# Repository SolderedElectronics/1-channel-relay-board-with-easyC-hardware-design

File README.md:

# 1-channel relay board qwiic Hardware Design

## About the Product

|  |
| :----------------------------------------------------------: |
| [Buy 1-channel relay board qwiic](https://www.solde.red/333021) |

Did you ever wanted to turn on and off a device that needs large current or voltage? Whether operating on DC or AC, a relay is what you need. A relay is actually an electronic switch that is activated by a signal we send from a Dasduino or Arduino. This module further simplifies the whole process because it contains everything you need for the relay to work, and you just have to connect it to the microcontroller and power supply. You don’t have to think about voltages and currents, insulation between high and low voltage or grounding, everything is already taken care of on the board.

This board has easyC connector. Thanks to qwiic ecosystem, this board can be connected using off-the-shelf cables, without soldering. Controlling the is as simple as it gets, too.

---

## Repository Contents

This repository contains all design files for 1-channel relay board qwiic, organized as follows:

- **`CAD` folder**: Contains KiCAD design files, including:
  - Schematics
  - PCB layout
  - Panel PCB layout
  - Source 3D files in Fusion360, if any
  - All files are sorted by version with a detailed change log.
- **`OUTPUTS` folder**: Includes all production-ready files, such as:
  - Bill of Materials (BOM) and interactive BOM (iBOM)
  - PDF versions of schematics
  - 3D `.step` file of the board
  - 3D-printable models
  - Gerber files for PCB manufacturing
  - Image of the pinout of the board
  - Product image
  - Compliance, legal and generic sales documents

Refer to the `Change Log` in the CAD folder for details about updates between versions.

---

## Learn More About the Product

Beyond the repository, explore the following resources:

### Soldered Verify

The **Soldered Verify** system ensures every board you purchase from Soldered is fully functional. It also provides access to exclusive test data for your product. To get started, find the unique Soldered Verify ID on your product's packaging and enter the ID on the [Soldered Verify page](https://soldered.com/verify/) to access test results and additional product details.

### Soldered Community

Soldered Community is your go-to place for technical support. Our engineers track and answer all questions posted there, and it’s a great space for the maker community. Get answers to your questions and solutions for your challenges at [Soldered Community](https://soldered.com/community).

### solde.red

solde.red is an ultimate URL shortener and information hub. Access it by typing solde.red/ followed by your product SKU, e.g., [solde.red/333000](https://solde.red/333000), to find getting-started guides, datasheets, open-source hardware and software files, certifications, images, pinouts, and more. Read more about the shortener [here](https://solde.red/info/).

---

## Contributing

Contributions are welcome! Here’s how you can get involved:

- Submit pull requests to enhance the design or fix issues.
- Report bugs or problems by opening an issue.

We encourage community collaboration to make this product even better.

---

## About Soldered

[Soldered for Makers](https://soldered.com) specializes in designing and manufacturing electronic products tailored for enthusiasts, ranging from hobbyists to professionals. Our portfolio includes electronic boards, sensors, and actuators that are widely utilized in fields such as microelectronics, mechatronics, robotics, programming, and IoT. Every product we offer is designed in-house and built upon open-source hardware and software platforms. Proudly certified and manufactured within the European Union, our catalog likely includes the product you need for your project.

We complement these products with comprehensive tutorials and manuals, product descriptions, schematics, programming codes, and project examples. Our round-the-clock [customer and technical support](https://soldered.com/community) is available for all our products, irrespective of the sales channel. Soldered’s success and services reflect our maker community’s unwavering [trust](https://www.trustpilot.com/review/soldered.com), for which we are deeply grateful. Join our community and create using Soldered products.

---

## License

All Soldered open-source hardware (OSH) is under The TAPR Open Hardware License. Read more in the LICENSE file located in this repository.

**Disclaimer:**

No warranty - all designs in this repository are distributed in the hope that they will be useful, but without any warranty. They are provided "AS IS", therefore without warranty of any kind, either expressed or implied. The entire quality and performance of what you do with the contents of this repository are your responsibility. In no event Soldered Electronics will be liable for your damages, or losses, including any general, special, incidental, or consequential damage arising out of the use or inability to use the contents of this repository. 

---

## Have fun!

Thank you for your support from your fellow makers at Soldered Electronics.

Happy Making!

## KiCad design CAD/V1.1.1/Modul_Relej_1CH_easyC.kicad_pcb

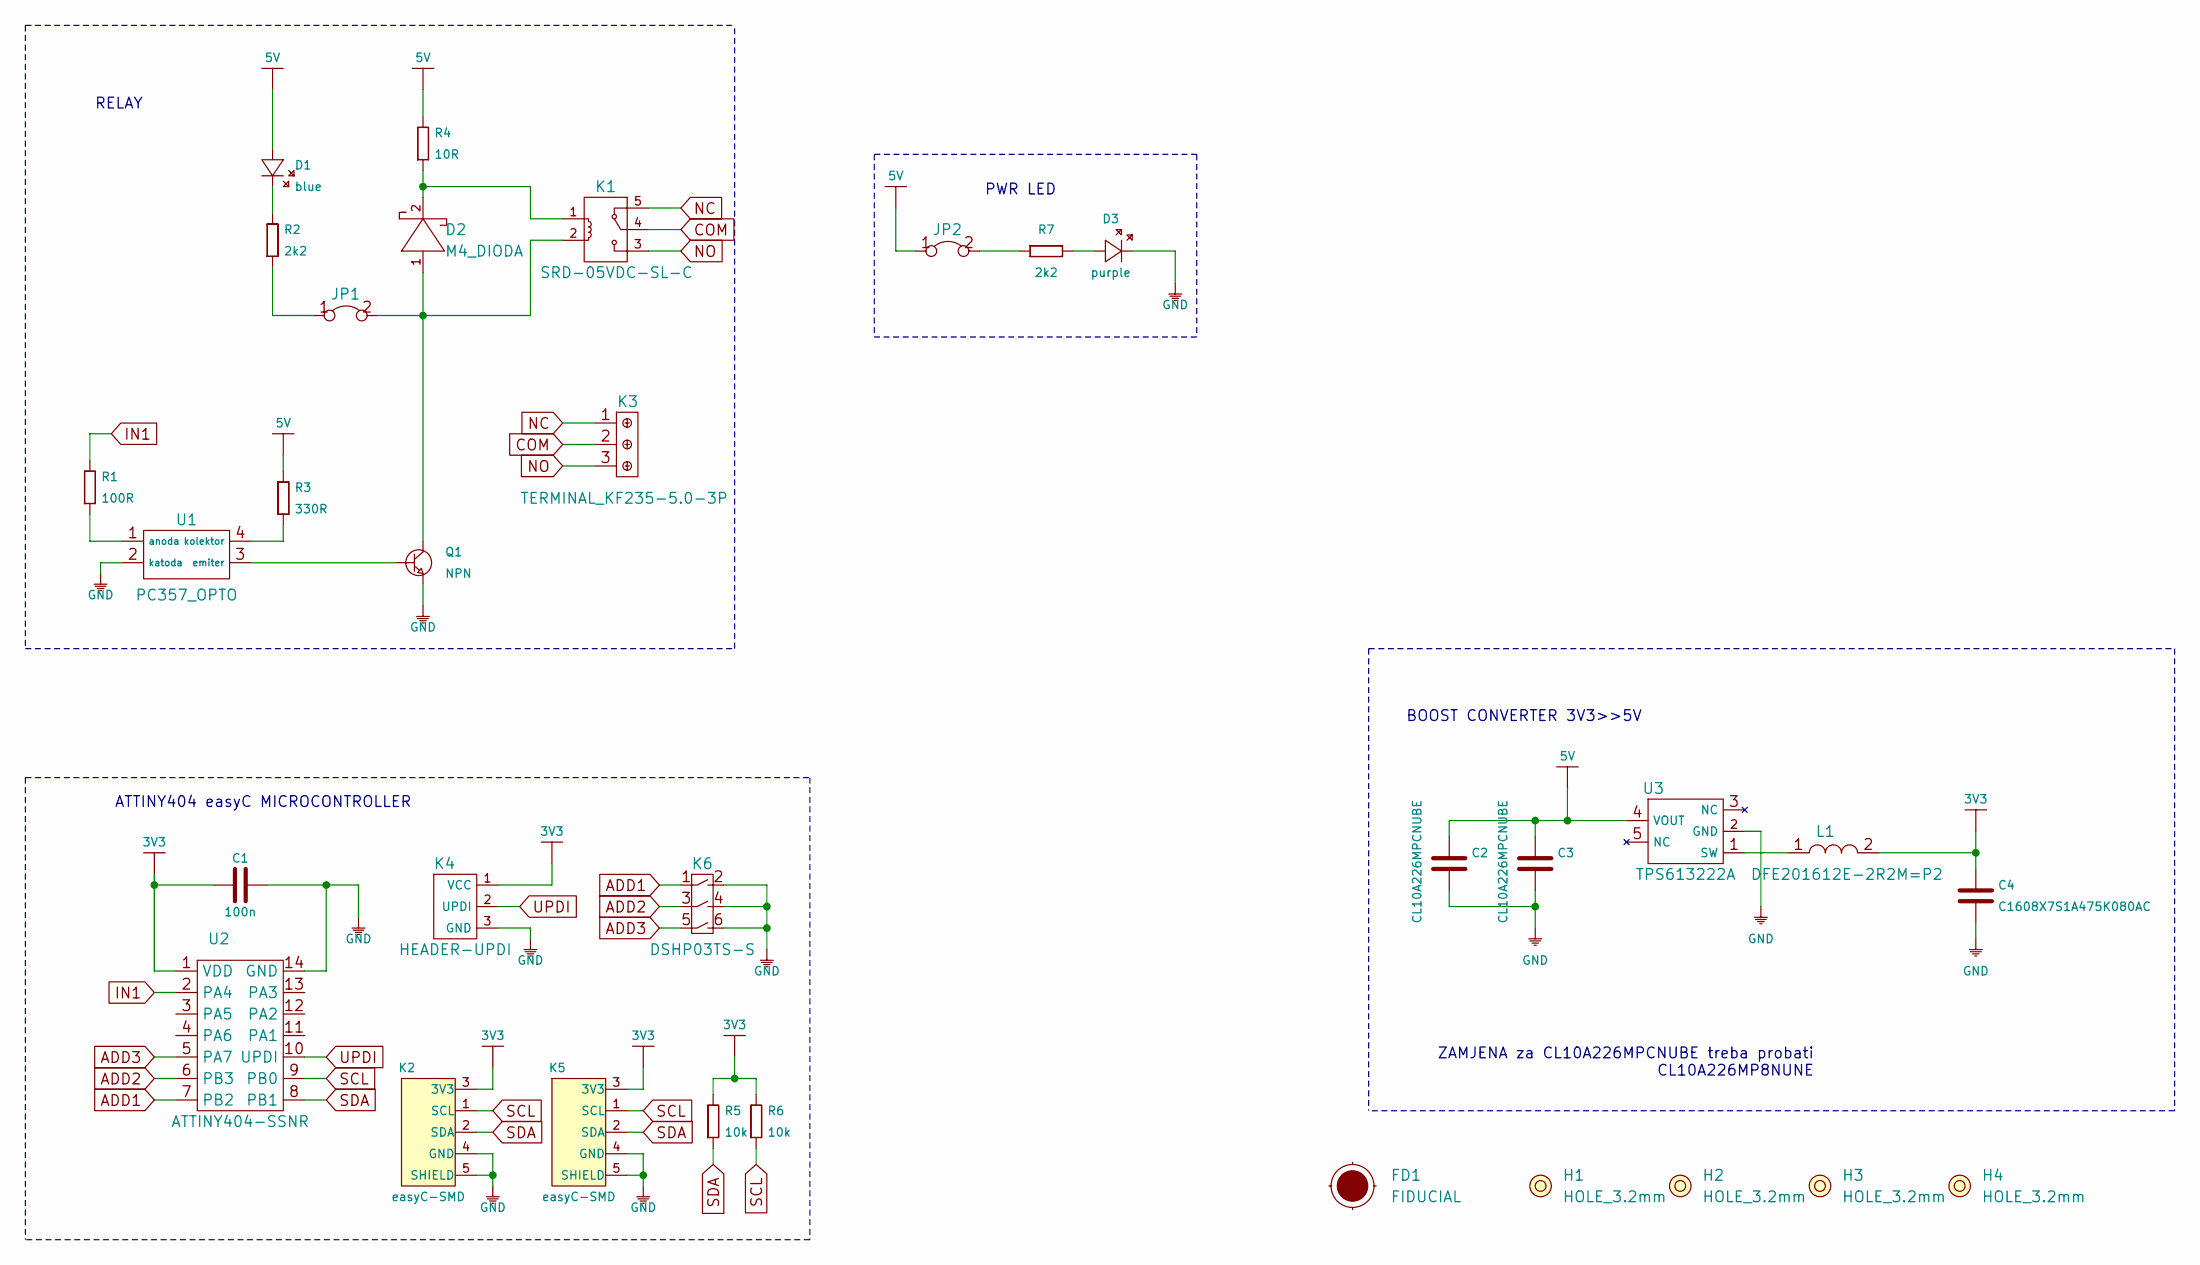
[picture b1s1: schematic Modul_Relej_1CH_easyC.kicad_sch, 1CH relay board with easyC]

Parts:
C1: 100n; 0603C
C2, C3: CL10A226MPCNUBE; 0603C
C4: C1608X7S1A475K080AC; 0603C
D1: blue; 0402LED
D2: M4_DIODA
D3: purple; 0402LED
FD1: FIDUCIAL; FIDUCIAL_23
H1, H2, H3, H4: HOLE_3.2mm
JP1, JP2: SMD-JUMPER-CONNECTED_TRACE_SLODERMASK
K1: SRD-05VDC-SL-C; SRD_RELAY_5V
K2, K5: easyC-SMD; easyC-connector
K3: TERMINAL_KF235-5.0-3P
K4: HEADER-UPDI
K6: DSHP03TS-S
L1: DFE201612E-2R2M=P2; 0806L
Q1: NPN; SOT-23-3
R1: 100R; 0603R
R2, R7: 2k2; 0402R
R3: 330R; 0603R
R4: 10R; 0603R
R5, R6: 10k; 0603R
U1: PC357_OPTO
U2: ATTINY404-SSNR; SOIC-14
U3: TPS613222A; tps613222a

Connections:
3V3: C1.1, C4.2, K2.3 (3V3), K4.1 (VCC), K5.3 (3V3), L1.2, R5.2, R6.2, U2.1 (VDD)
5V: C2.2, C3.2, D1.1 (A), JP2.1, R3.2, R4.2, U3.4 (VOUT)
ADD1: K6.1, U2.7 (PB2)
ADD2: K6.3, U2.6 (PB3)
ADD3: K6.5, U2.5 (PA7)
COM: K1.4, K3.2
GND: C1.2, C2.1, C3.1, C4.1, D3.2 (K), K2.4 (GND), K2.5 (SHIELD), K4.3 (GND), K5.4 (GND), K5.5 (SHIELD), K6.2, K6.4, K6.6, Q1.2 (E), U1.2 (katoda), U2.14 (GND), U3.2 (GND)
IN1: R1.2, U2.2 (PA4)
NC: K1.5, K3.1
NO: K1.3, K3.3
unnamed: D1.2 (K), R2.2
unnamed: D2.1 (A), JP1.2, K1.2, Q1.3 (C)
unnamed: D2.2 (K), K1.1, R4.1
unnamed: D3.1 (A), R7.2
unnamed: JP1.1, R2.1
unnamed: JP2.2, R7.1
unnamed: L1.1, U3.1 (SW)
unnamed: Q1.1 (B), U1.3 (emiter)
unnamed: R1.1, U1.1 (anoda)
unnamed: R3.1, U1.4 (kolektor)
SCL: K2.1 (SCL), K5.1 (SCL), R6.1, U2.9 (PB0)
SDA: K2.2 (SDA), K5.2 (SDA), R5.1, U2.8 (PB1)
UPDI: K4.2 (UPDI), U2.10 (UPDI)

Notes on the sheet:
ATTINY404 easyC MICROCONTROLLER
RELAY
ZAMJENA za CL10A226MPCNUBE treba probati CL10A226MP8NUNE
PWR LED
BOOST CONVERTER 3V3>>5V

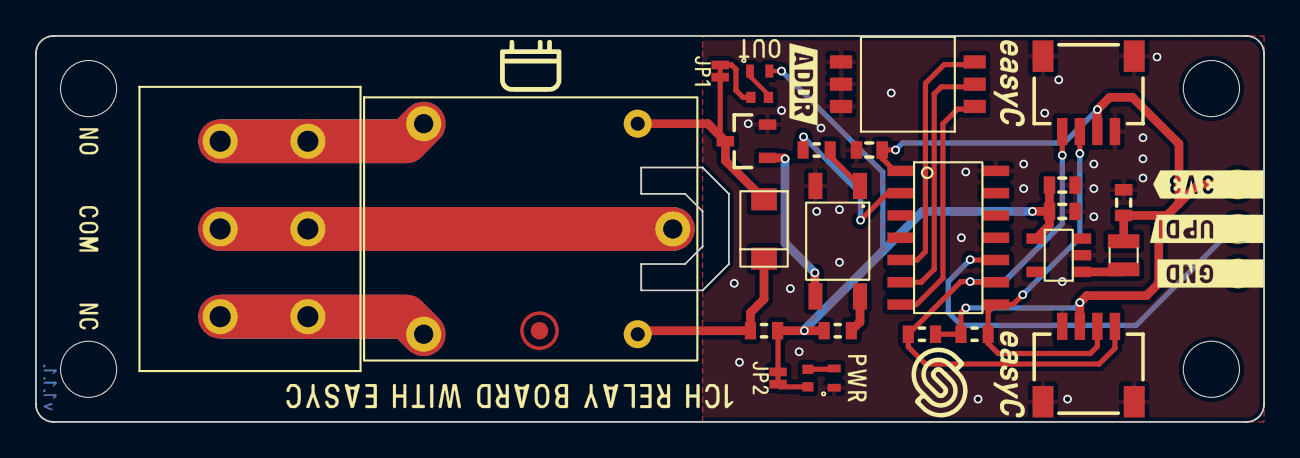
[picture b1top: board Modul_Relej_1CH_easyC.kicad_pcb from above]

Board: 2 copper layers, 70.0 x 22.0 mm, 32 parts (0 on the bottom side), 23 nets.

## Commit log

2022-08-06 Updating open source files.
